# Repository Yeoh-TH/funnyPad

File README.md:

# Simple HackPad
</img>
## PCB
</img>
Here is my PCB, it consists of simple push down switches that can be soldered on

## Schematic
</img>
This schematic is a basic diagram of my keypad, nothing too crazy

## The Legal Case in mind
</img>
This case has room for a SEEED micronctroller, keycaps, and space for extra modifications (OLED display on top for future development)

## BOM
Some parts here are extras within the approved parts lists just in case I mess up
- Seeed XIAO RP2040
- 10 MX-Style Switches
- 10 Blank DSA keycaps
- 10 SK6812 MINI-E LEDs 
- 6 M3x16mm screws
- 6 M3x5mx4mm heatset inserts
- 2 EC11 Rotary encoders 
- 15 Through-hole 1N4148 Diodes
- 1 0.91 inch OLED display (Extra parts so I can play around in the future:)

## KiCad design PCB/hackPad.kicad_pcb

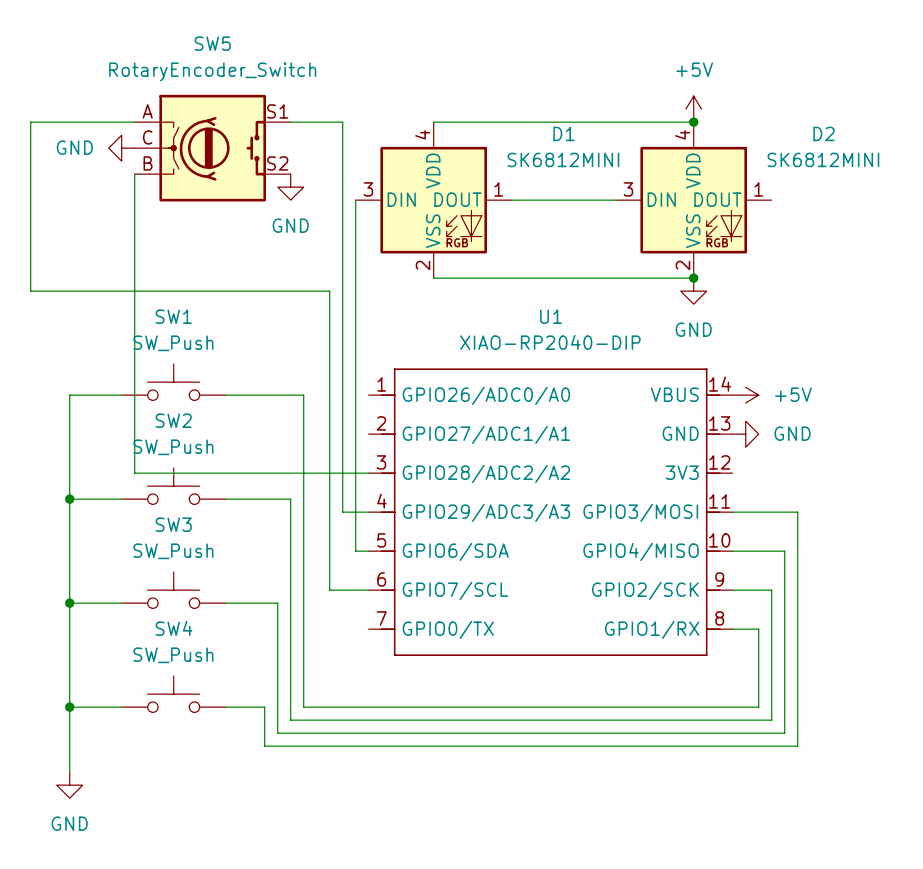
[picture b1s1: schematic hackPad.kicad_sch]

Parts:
D1, D2: SK6812MINI; LED_SK6812MINI_PLCC4_3.5x3.5mm_P1.75mm
SW1, SW2, SW3, SW4: SW_Push; SW_Cherry_MX_1.00u_PCB
SW5: RotaryEncoder_Switch; RotaryEncoder_Alps_EC11E-Switch_Vertical_H20mm
U1: XIAO-RP2040-DIP

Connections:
+5V: D1.4 (VDD), D2.4 (VDD), U1.14 (VBUS)
GND: D1.2 (VSS), D2.2 (VSS), SW1.1, SW2.1, SW3.1, SW4.1, SW5.C, SW5.S2, U1.13 (GND)
unnamed: D1.3 (DIN), U1.5 (GPIO6/SDA)
unnamed: D1.1 (DOUT), D2.3 (DIN)
unnamed: SW1.2, U1.8 (GPIO1/RX)
unnamed: SW2.2, U1.9 (GPIO2/SCK)
unnamed: SW4.2, U1.11 (GPIO3/MOSI)
unnamed: SW3.2, U1.10 (GPIO4/MISO)
unnamed: SW5.A, U1.6 (GPIO7/SCL)
unnamed: SW5.B, U1.3 (GPIO28/ADC2/A2)
unnamed: SW5.S1, U1.4 (GPIO29/ADC3/A3)

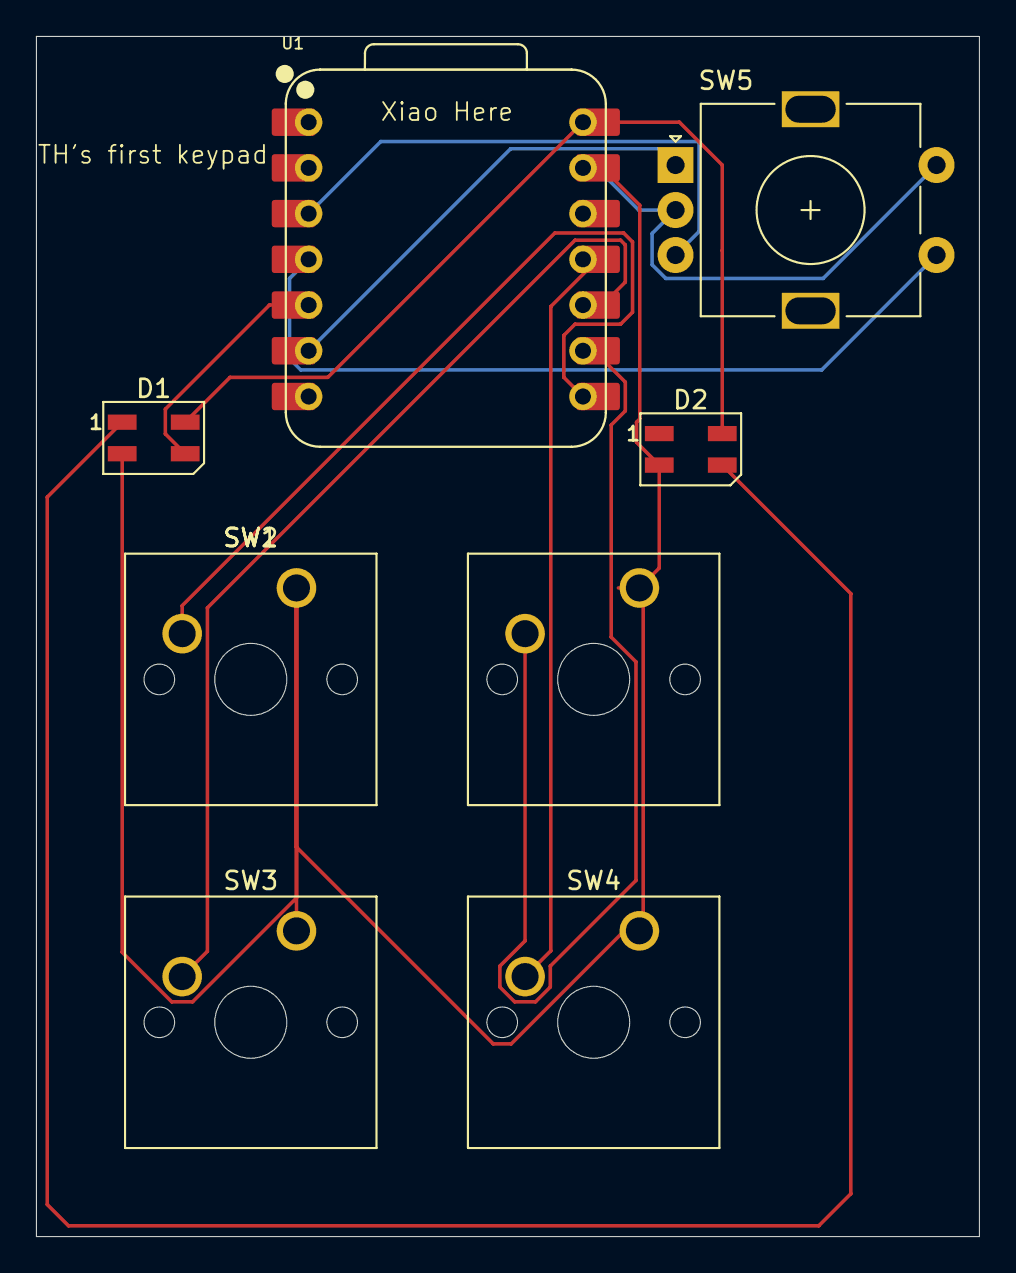
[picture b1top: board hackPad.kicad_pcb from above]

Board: 2 copper layers, 52.4 x 66.7 mm, 8 parts (0 on the bottom side), 11 nets.

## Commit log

2025-07-12 Submission of hackPad
2025-07-12 Remade to add more changes to make the pad more unique
2025-07-12 firmware work
